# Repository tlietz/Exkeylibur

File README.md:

# Exkeylibur

```markdown
I froze your switches and made Exkeylibur,
and pushed it onto Github forever.
It stays there like Excalibur,
Are you its Arthur?
Say you are.

Take the cool, dark, steeled board,
Steal it, sheath it, in your workflow.
All would drown their other keebs to be together.
Must they breathe? 'Cause typing feels like heaven.
```

*Based off of ['Excalibur' - by David Brent](https://www.youtube.com/watch?v=634TC7Feku4)*

I would like to thank the honorable [Ferris Sweep](https://github.com/davidphilipbarr/Sweep), for without you, the Exkeylibur would have no pcb layout.

## Prelude

An Exkeylibur is a 36-key, diodeless, wireless-only keyboard with Ferris stagger and a reversible PCB.

An Exkeylibur can be wielded without a sheath, however, you are encouraged to create one.

A promicro, or any other non-wireless microcontroller drop-in for the promicro, is **not** supported. This is because the GPIO pin that would normally go to a TRRS jack
now goes to an extra switch.

## Features

- Wireless only
- No diodes required
- 36 keys
- Reversible PCB
- Ferris stagger
- Choc-spaced

## V2 Changes

- Rotated outer thumb key by 90 degrees to support 1.5u keycap
- Added room to place rubber feet
- Moved home thumb key to be between the two thumb keys of the Ferris Sweep
- Placed reset button in a position that can be easily pressed with finger
- Slightly increased reset button pcb pad spacing to support more button sizes

## Firmware Build Instructions

Edit the `ZMK_PATH`, `MCU`, and `KEEB` variables in `Makefile`

If this is your first time, run `make pristine`.
Next time, you can just do `make`.

The `firmware/` directory will have the left and right firmware files.

The keymap here may change in the future.

## Images

### V2

### V1

#### Original

#### Hilt

#### Dagger

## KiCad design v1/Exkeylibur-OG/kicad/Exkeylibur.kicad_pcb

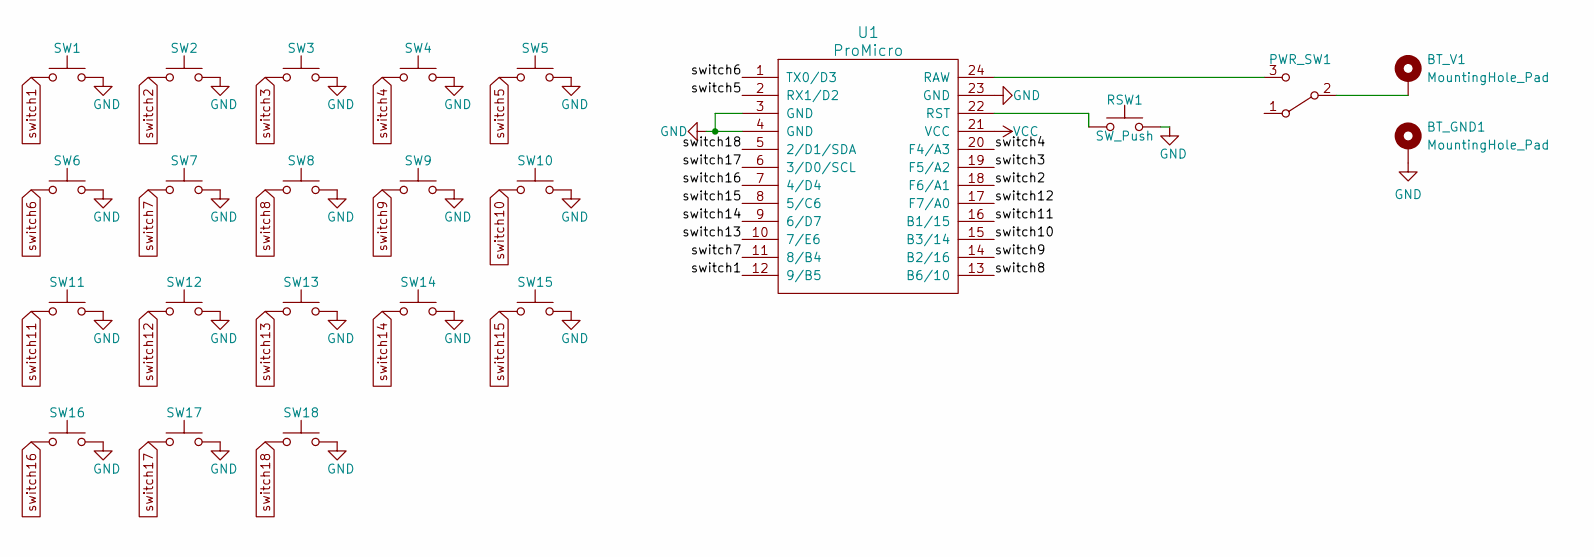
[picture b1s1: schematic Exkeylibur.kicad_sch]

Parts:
BT_GND1: MountingHole_Pad; bat_gnd_mountingHole
BT_V1: MountingHole_Pad; Bat_MountingHole
PWR_SW1: SW_SPDT; SPDT_C128955
RSW1: SW_Push; reset_switch
SW1, SW2, SW3, SW4, SW5, SW6, SW7, SW8, SW9, SW10, SW11, SW12, SW13, SW14, SW15, SW16, SW17, SW18: SW_Push; choc_switch_reversible
U1: ProMicro; ProMicro_v3_min

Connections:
GND: BT_GND1.1, RSW1.2, SW1.2, SW2.2, SW3.2, SW4.2, SW5.2, SW6.2, SW7.2, SW8.2, SW9.2, SW10.2, SW11.2, SW12.2, SW13.2, SW14.2, SW15.2, SW16.2, SW17.2, SW18.2, U1.3 (GND), U1.4 (GND), U1.23 (GND); also elsewhere on the board
unnamed 1: BT_V1.1, PWR_SW1.2 (B); also elsewhere on the board
unnamed 2: PWR_SW1.3 (C), U1.24 (RAW); also elsewhere on the board
unnamed 3: RSW1.1, U1.22 (RST); also elsewhere on the board
VCC: U1.21 (VCC)
switch1: SW1.1, U1.12 (9/B5)
switch2: SW2.1, U1.18 (F6/A1)
switch3: SW3.1, U1.19 (F5/A2)
switch4: SW4.1, U1.20 (F4/A3)
switch5: SW5.1, U1.2 (RX1/D2)
switch6: SW6.1, U1.1 (TX0/D3)
switch7: SW7.1, U1.11 (8/B4)
switch8: SW8.1, U1.13 (B6/10)
switch9: SW9.1, U1.14 (B2/16)
switch10: SW10.1, U1.15 (B3/14)
switch11: SW11.1, U1.16 (B1/15)
switch12: SW12.1, U1.17 (F7/A0)
switch13: SW13.1, U1.10 (7/E6)
switch14: SW14.1, U1.9 (6/D7)
switch15: SW15.1, U1.8 (5/C6)
switch16: SW16.1, U1.7 (4/D4)
switch17: SW17.1, U1.6 (3/D0/SCL)
switch18: SW18.1, U1.5 (2/D1/SDA)

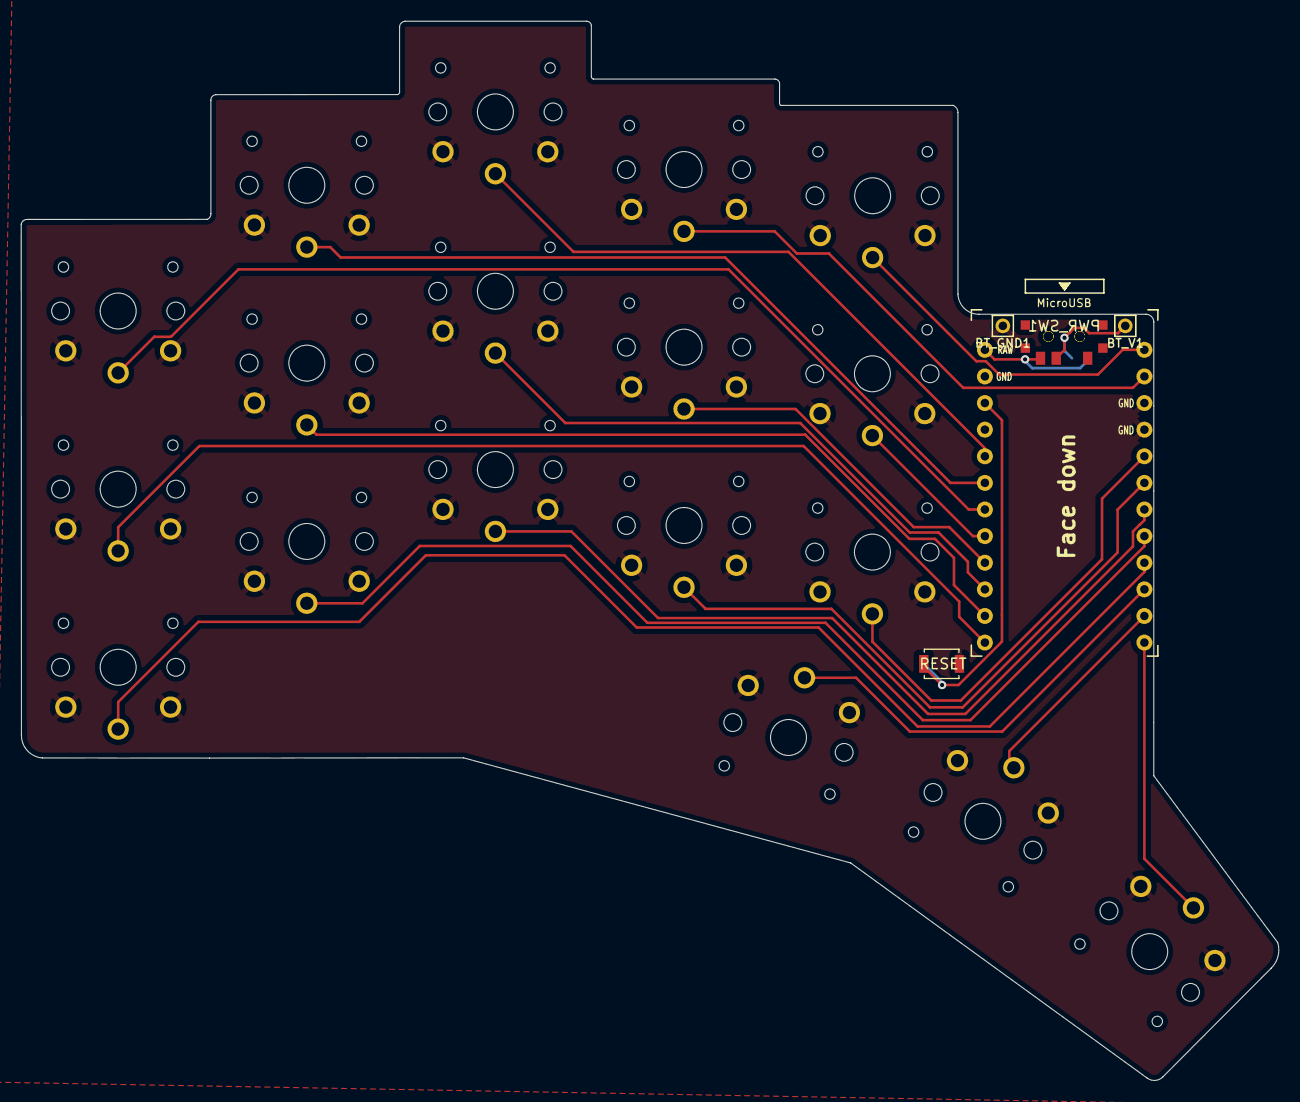
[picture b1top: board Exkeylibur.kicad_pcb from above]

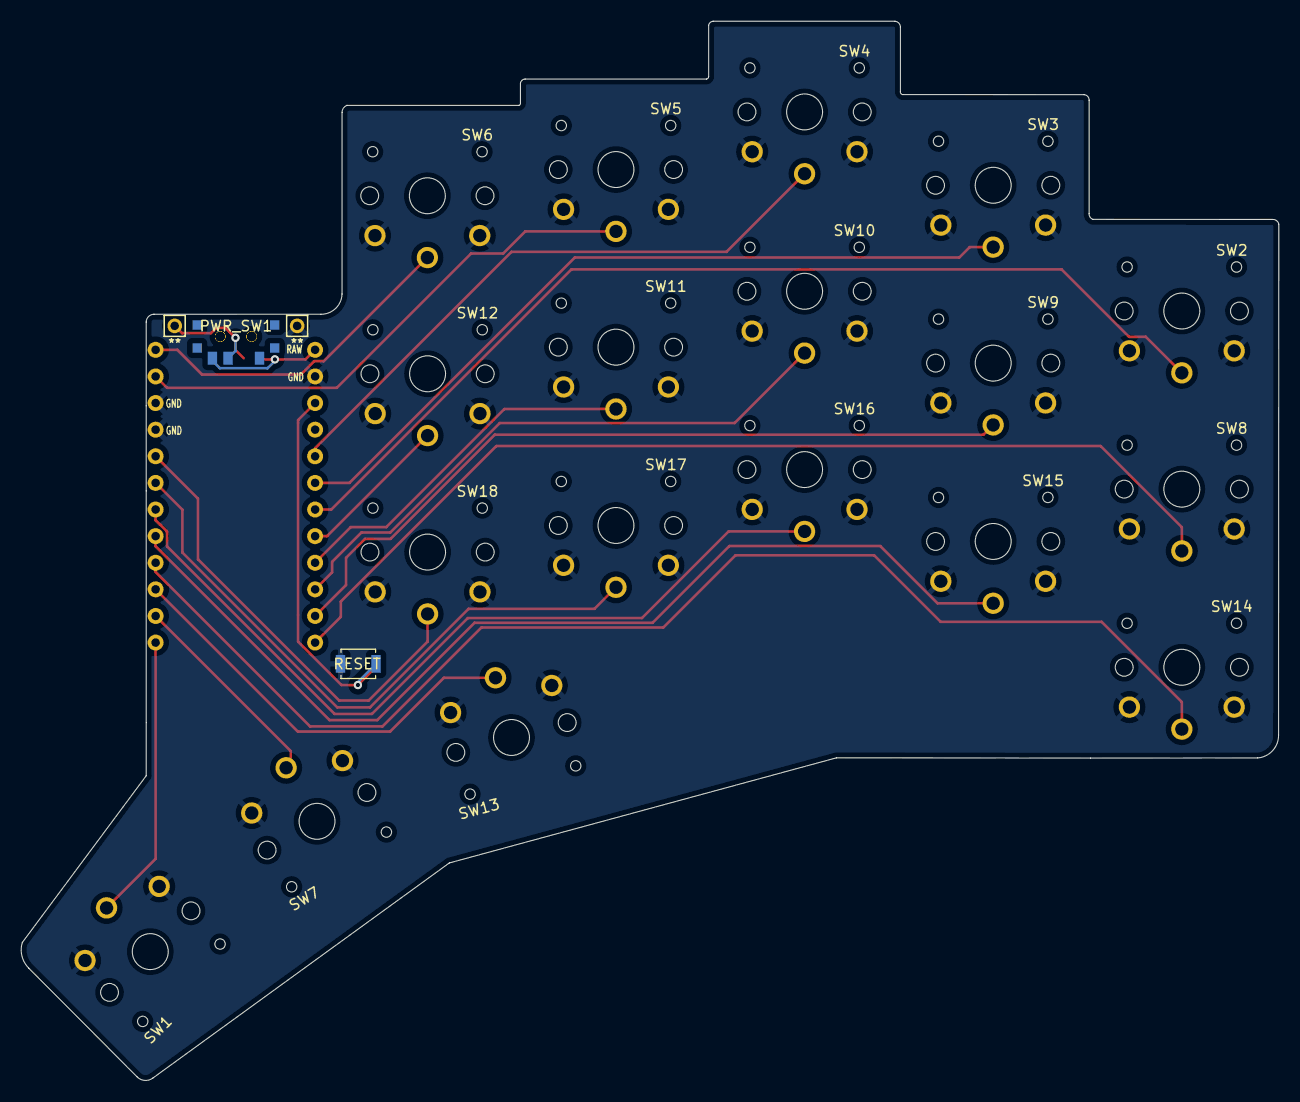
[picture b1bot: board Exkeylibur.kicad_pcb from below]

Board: 2 copper layers, 120.0 x 101.1 mm, 25 parts (2 on the bottom side), 22 nets.

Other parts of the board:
PWR_SW1#2: SW_SPDT; SPDT_C128955
RSW1#2: SW_Push; reset_switch

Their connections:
GND: RSW1#2.2; also elsewhere on the board
unnamed 1: PWR_SW1#2.2 (B); also elsewhere on the board
unnamed 2: PWR_SW1#2.3 (C); also elsewhere on the board
unnamed 3: RSW1#2.1; also elsewhere on the board

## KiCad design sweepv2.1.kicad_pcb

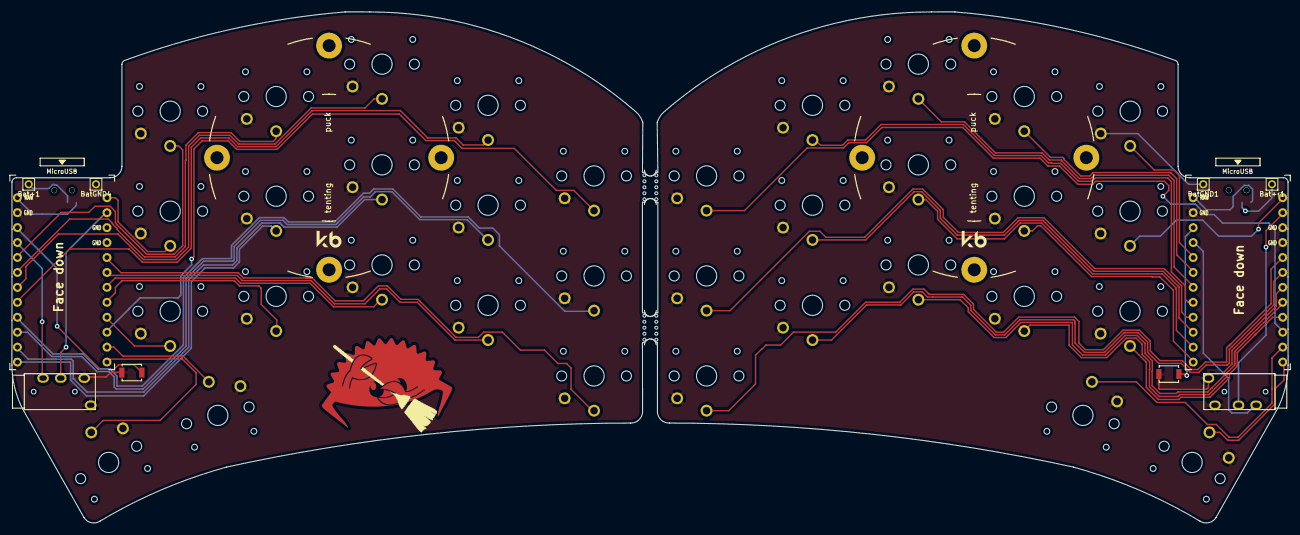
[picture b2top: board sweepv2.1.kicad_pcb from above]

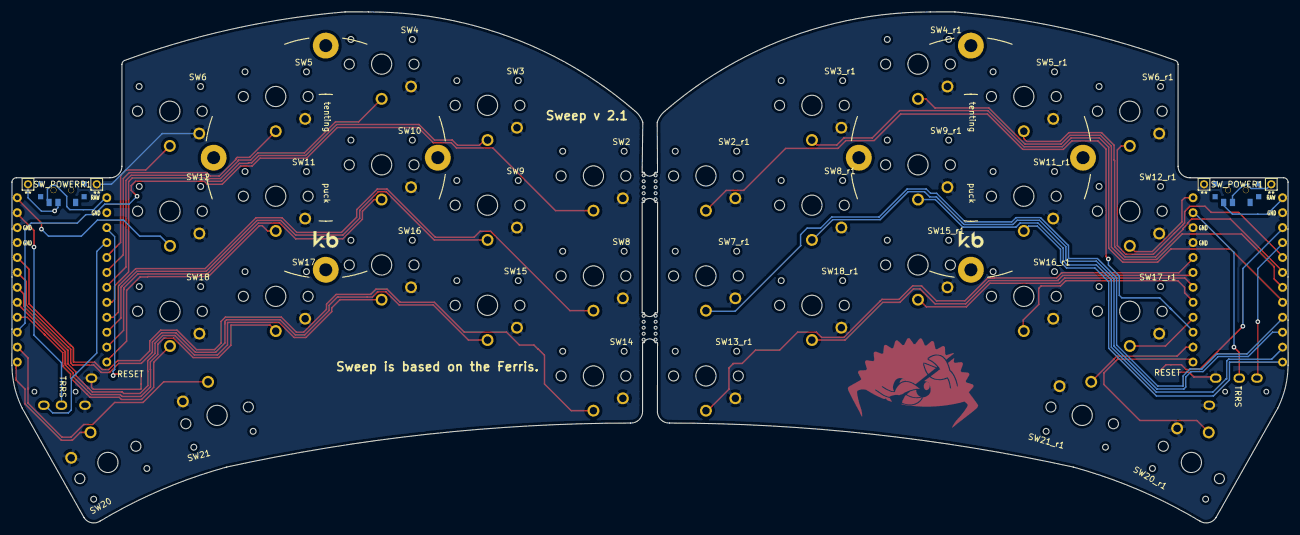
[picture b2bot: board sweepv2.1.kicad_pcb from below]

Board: 2 copper layers, 216.9 x 86.9 mm, 48 parts (2 on the bottom side), 43 nets.

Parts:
Bat+1: MountingHole_Pad; 1pin_conn
Bat+r1: MountingHole_Pad; 1pin_conn
BatGND1, BatGND4: MountingHole_Pad; 1pin_conn
J1, J2: AudioJack4dpb; TRRS-PJ-320A
RSW1, RSW2: SW_Push; SW_SPST_B3U-1000P
SW2, SW2_r1, SW3, SW3_r1, SW4, SW4_r1, SW5, SW5_r1, SW6, SW6_r1, SW7_r1, SW8, SW8_r1, SW9, SW9_r1, SW10, SW11, SW11_r1, SW12, SW12_r1, SW13_r1, SW14, SW15, SW15_r1, SW16, SW16_r1, SW17, SW17_r1, SW18, SW18_r1, SW20, SW20_r1, SW21, SW21_r1: SW_Push; SW_PG1350_nonrev_DPB
SW_POWER1: SW_SPDT; SPDT_C128955
SW_POWERR1: SW_SPDT; SPDT_C128955
U1, U2: ProMicro-kbd; ProMicro_v3_min
mouse-bite-2mm-slot, mouse-bite-2mm-slot#2: VAL**; mouse-bite-5mm-slot-with-space-for-track

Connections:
BT+: Bat+1.1, SW_POWER1.2
BT+_r: Bat+r1.1, SW_POWERR1.2
Switch1: SW2.1, U1.10
Switch1_r: SW2_r1.1, U2.10
Switch2: SW3.1, U1.17
Switch2_r: SW3_r1.1, U2.17
Switch3: SW4.1, U1.18
Switch3_r: SW4_r1.1, U2.18
Switch4: SW5.1, U1.19
Switch4_r: SW5_r1.1, U2.19
Switch5: SW6.1, U1.20
Switch5_r: SW6_r1.1, U2.20
Switch6: SW8.1, U1.16
Switch6_r: SW7_r1.1, U2.16
Switch7: SW9.1, U1.15
Switch7_r: SW8_r1.1, U2.15
Switch8: SW10.1, U1.14
Switch8_r: SW9_r1.1, U2.14
Switch9: SW11.1, U1.13
Switch9_r: SW11_r1.1, U2.13
Switch10: SW12.1, U1.1
Switch10_r: SW12_r1.1, U2.1
Switch11: SW14.1, U1.5
Switch11_r: SW13_r1.1, U2.5
Switch12: SW15.1, U1.6
Switch12_r: SW18_r1.1, U2.6
Switch13: SW16.1, U1.7
Switch13_r: SW15_r1.1, U2.7
Switch14: SW17.1, U1.8
Switch14_r: SW16_r1.1, U2.8
Switch15: SW18.1, U1.9
Switch15_r: SW17_r1.1, U2.9
Switch16: SW21.1, U1.11
Switch16_r: SW21_r1.1, U2.11
Switch17: SW20.1, U1.12
Switch17_r: SW20_r1.1, U2.12
Switch18: J2.R1, U1.2
Switch18_r: J1.R1, U2.2
gnd: BatGND1.1, BatGND4.1, J1.S, J1.T, J2.S, J2.T, RSW1.1, RSW2.1, SW2.2, SW2_r1.2, SW3.2, SW3_r1.2, SW4.2, SW4_r1.2, SW5.2, SW5_r1.2, SW6.2, SW6_r1.2, SW7_r1.2, SW8.2, SW8_r1.2, SW9.2, SW9_r1.2, SW10.2, SW11.2, SW11_r1.2, SW12.2, SW12_r1.2, SW13_r1.2, SW14.2, SW15.2, SW15_r1.2, SW16.2, SW16_r1.2, SW17.2, SW17_r1.2, SW18.2, SW18_r1.2, SW20.2, SW20_r1.2, SW21.2, SW21_r1.2, U1.3, U1.4, U1.23, U2.3, U2.4, U2.23
raw: SW_POWER1.3, SW_POWERR1.3, U1.24, U2.24
reset: RSW1.2, U1.22
reset_r: RSW2.2, U2.22
vcc: J1.R2, J2.R2, U1.21, U2.21

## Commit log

2022-02-24 eliteC TRRS and switches left side on schematic
2022-02-24 typo fix on switch ref des
2022-02-24 add all untracked
2022-02-24 gitignore
2022-02-24 fix gitignore
2022-02-24 add more gitignore
2022-02-24 remove cached and change gitignore
2022-02-25 connect OLED to MC
2022-02-25 make right side schematic
2022-02-25 add no connects
2022-02-25 add annotations for left and right
2022-02-25 revert pcb
2022-03-02 changes outlay to include 4 thumb keys
2022-03-03 rework schematic to be compatible with promicro only
2022-03-03 pcb reversible layout
2022-03-04 traces routed
2022-03-04 copper pour
2022-03-04 backannotate to schematic:
2022-03-04 save pcb
2022-03-04 gerber zipped and repo structure in place
2022-03-04 poem
2022-03-04 change poem
2022-03-04 Improve poem
2022-03-04 poem upgrade
2022-03-04 poem final
2022-03-04 poem
    change poem
    Improve poem
    poem upgrade
    poem final
2022-03-04 create hilted and compressed versions of exkeylibur
2022-03-05 fix some errors with the board outline
2022-03-06 add images
2022-03-06 put images in readme
2022-03-06 fix hilt pcb image link
2022-03-11 add link to firmware
2022-03-18 update readme with todos for version 2
2022-03-18 add more to readme, and organize v1 projects
2022-03-18 add features section
2022-03-19 finish v2
2022-03-19 compress new gerber
2022-03-19 add more room for the 1.5u keycap
2022-03-19 add image of v2
2022-03-19 fix some readme stuff
2022-03-19 add zmk-config
2022-03-19 remove zmk
2022-04-02 fix grounding issue with one of the switches
